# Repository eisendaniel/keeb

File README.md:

# un**ORTHO**dox

Devices

* UNO-XXX are main hosts, direct USB HID devices
* DOX-XXX are I2C expansion modules, connected via TRRS to the I2C bus and 5V power rails

## **UNO-W14** : 14x5 ortholinear keyboard

## **DOX**-XXX : I2C expansion modules

[TODO] ... space for future development

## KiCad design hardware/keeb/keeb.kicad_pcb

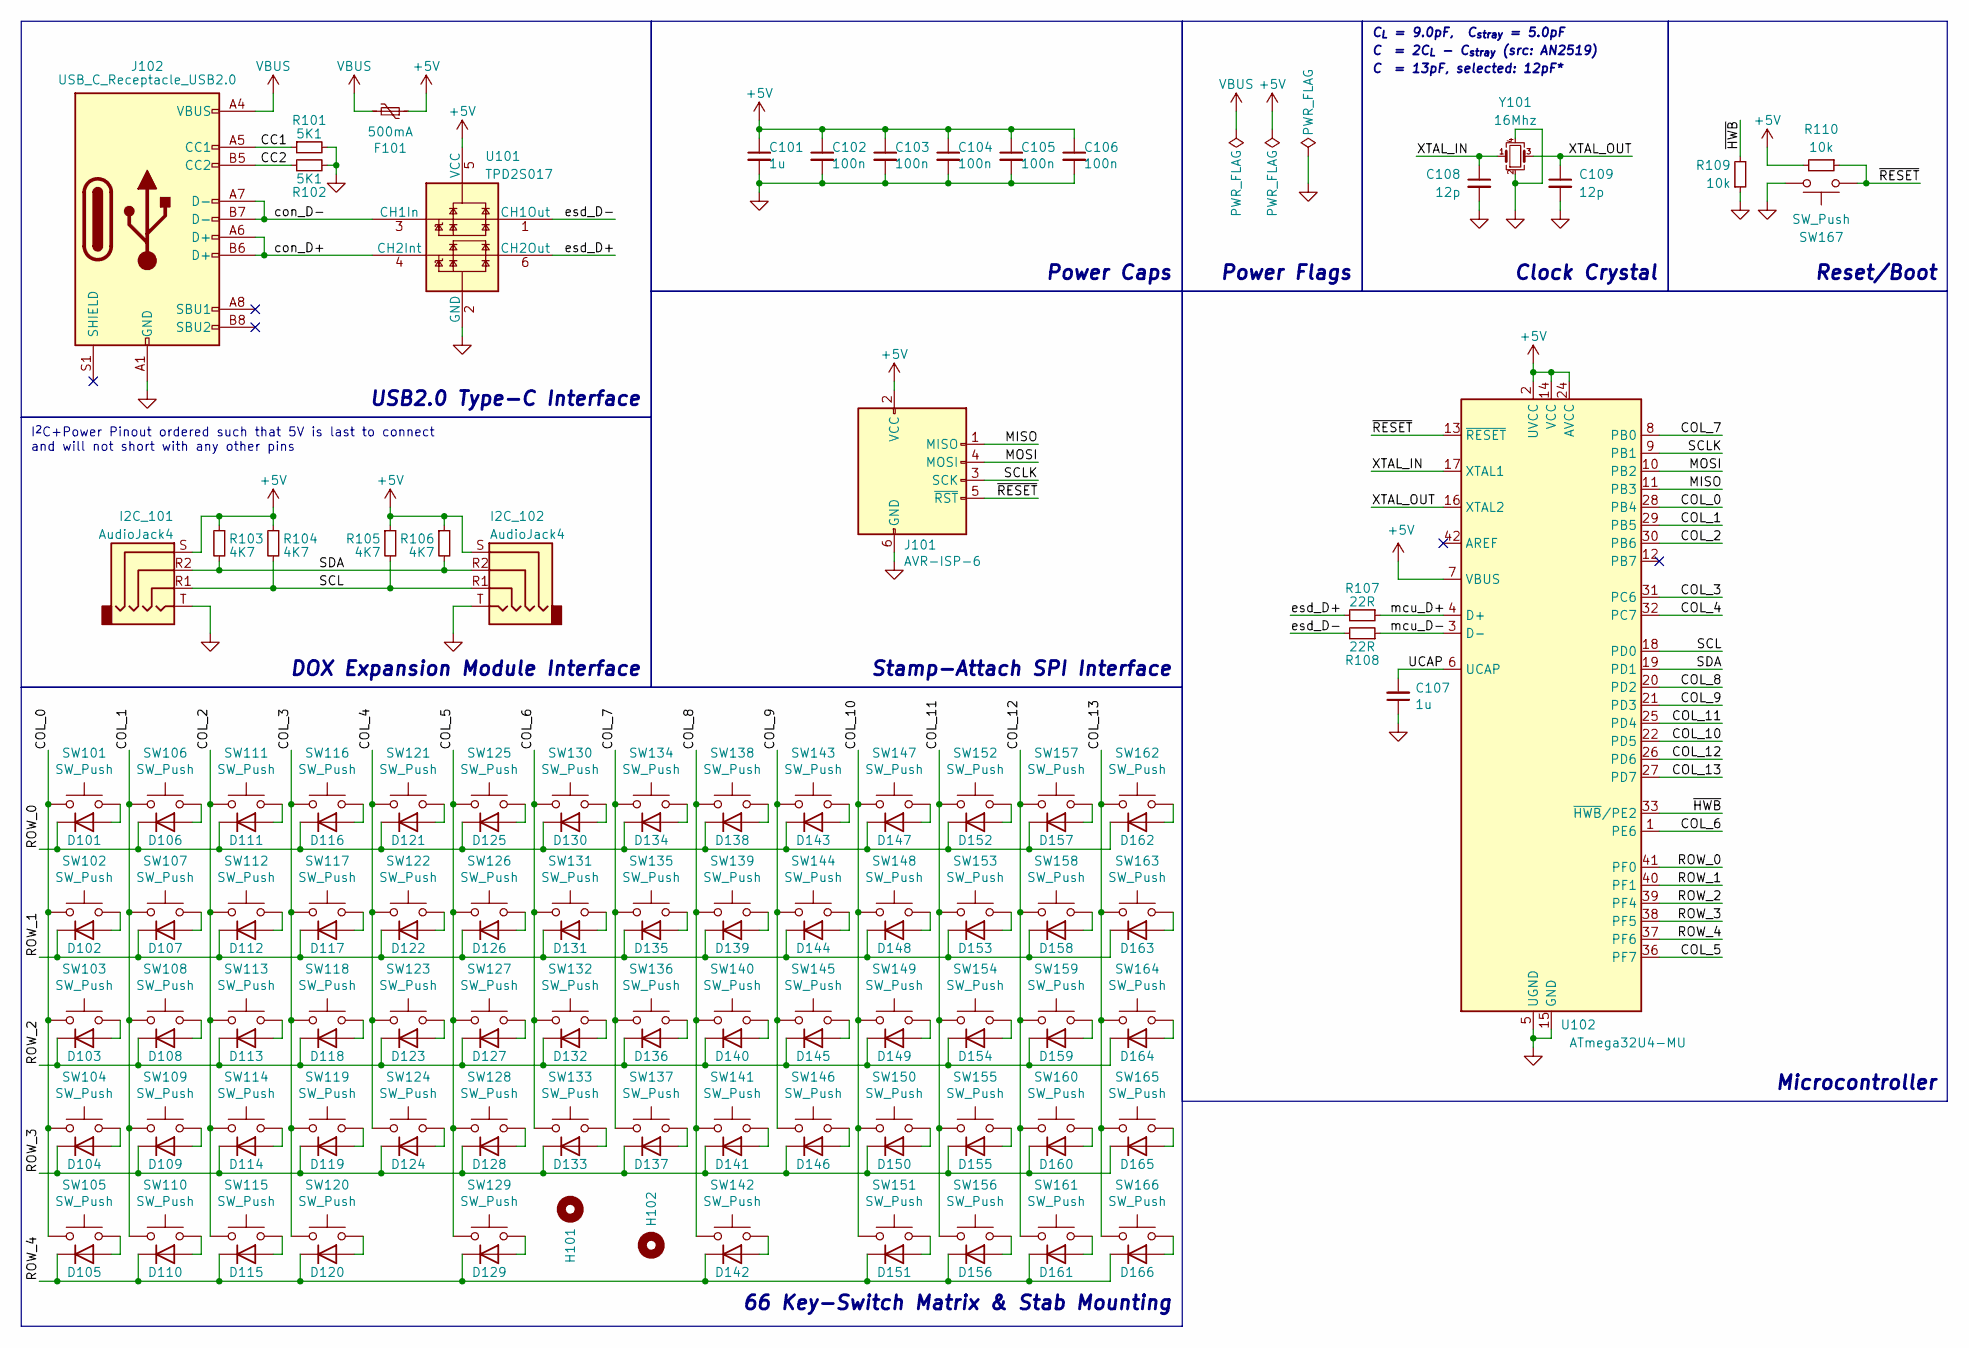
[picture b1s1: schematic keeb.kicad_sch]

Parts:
C101, C107: 1u; C_0603_1608Metric; LCSC # C15849
C102, C103, C104, C105, C106: 100n; C_0402_1005Metric; LCSC # C1525
C108, C109: 12p; C_0402_1005Metric; LCSC # C1547
D101, D102, D103, D104, D105, D106, D107, D108, D109, D110, D111, D112, D113, D114, D115, D116, D117, D118, D119, D120, D121, D122, D123, D124, D125, D126, D127, D128, D129, D130, D131, D132, D133, D134, D135, D136, D137, D138, D139, D140, D141, D142, D143, D144, D145, D146, D147, D148, D149, D150, D151, D152, D153, D154, D155, D156, D157, D158, D159, D160, D161, D162, D163, D164, D165, D166: D; D_SOD-123F; LCSC # C64898
F101: 500mA; Fuse_0603_1608Metric; LCSC # C369159
H101, H102: MountingHole; Stabilizer_Cherry_MX_3.00u
I2C_101, I2C_102: AudioJack4; Jack_3.5mm_TIC54-00177_Horizontal; LCSC # C388632
J101: AVR-ISP-6; Stamp-Attach_SA2030-IDC-NL_2x03_P1.27mm_Vertical
J102: USB_C_Receptacle_USB2.0; USB_C_Receptacle_HRO_TYPE-C-31-M-12; LCSC # C165948
R101, R102: 5K1; R_0402_1005Metric; LCSC # C25905
R103, R104, R105, R106: 4K7; R_0402_1005Metric; LCSC # C25900
R107, R108: 22R; R_0402_1005Metric; LCSC # C25092
R109, R110: 10k; R_0402_1005Metric; LCSC # C25744
SW101, SW102, SW103, SW104, SW105, SW106, SW107, SW108, SW109, SW110, SW111, SW112, SW113, SW114, SW115, SW116, SW117, SW118, SW119, SW120, SW121, SW122, SW123, SW124, SW125, SW126, SW127, SW128, SW129, SW130, SW131, SW132, SW133, SW134, SW135, SW136, SW137, SW138, SW139, SW140, SW141, SW142, SW143, SW144, SW145, SW146, SW147, SW148, SW149, SW150, SW151, SW152, SW153, SW154, SW155, SW156, SW157, SW158, SW159, SW160, SW161, SW162, SW163, SW164, SW165, SW166: SW_Push; SW_Cherry_MX_PCB_1.00u
SW167: SW_Push; SW_SPST_B3U-1000P; LCSC # C231329
U101: TPD2S017; SOT-23-6; LCSC # C880115
U102: ATmega32U4-MU; QFN-44-1EP_7x7mm_P0.5mm_EP5.2x5.2mm; LCSC # C112161
Y101: 16Mhz; Crystal_SMD_2016-4Pin_2.0x1.6mm; LCSC # C431146

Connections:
+5V: C101.1, C102.1, C103.1, C104.1, C105.1, C106.1, F101.1, I2C_101.S, I2C_102.S, J101.2 (VCC), R103.1, R104.1, R105.1, R106.1, R110.2, U101.5 (VCC), U102.2 (UVCC), U102.7 (VBUS), U102.14 (VCC), U102.24 (AVCC), U102.34 (VCC), U102.44 (AVCC)
/CC1: J102.A5 (CC1), R101.1
/CC2: J102.B5 (CC2), R102.1
/COL_0: SW101.1, SW102.1, SW103.1, SW104.1, SW105.1, U102.28 (PB4)
/COL_1: SW106.1, SW107.1, SW108.1, SW109.1, SW110.1, U102.29 (PB5)
/COL_2: SW111.1, SW112.1, SW113.1, SW114.1, SW115.1, U102.30 (PB6)
/COL_3: SW116.1, SW117.1, SW118.1, SW119.1, SW120.1, U102.31 (PC6)
/COL_4: SW121.1, SW122.1, SW123.1, SW124.1, U102.32 (PC7)
/COL_5: SW125.1, SW126.1, SW127.1, SW128.1, SW129.1, U102.36 (PF7)
/COL_6: SW130.1, SW131.1, SW132.1, SW133.1, U102.1 (PE6)
/COL_7: SW134.1, SW135.1, SW136.1, SW137.1, U102.8 (PB0)
/COL_8: SW138.1, SW139.1, SW140.1, SW141.1, SW142.1, U102.20 (PD2)
/COL_9: SW143.1, SW144.1, SW145.1, SW146.1, U102.21 (PD3)
/COL_10: SW147.1, SW148.1, SW149.1, SW150.1, SW151.1, U102.22 (PD5)
/COL_11: SW152.1, SW153.1, SW154.1, SW155.1, SW156.1, U102.25 (PD4)
/COL_12: SW157.1, SW158.1, SW159.1, SW160.1, SW161.1, U102.26 (PD6)
/COL_13: SW162.1, SW163.1, SW164.1, SW165.1, SW166.1, U102.27 (PD7)
/MISO: J101.1 (MISO), U102.11 (PB3)
/MOSI: J101.4 (MOSI), U102.10 (PB2)
/ROW_0: D101.1 (K), D106.1 (K), D111.1 (K), D116.1 (K), D121.1 (K), D125.1 (K), D130.1 (K), D134.1 (K), D138.1 (K), D143.1 (K), D147.1 (K), D152.1 (K), D157.1 (K), D162.1 (K), U102.41 (PF0)
/ROW_1: D102.1 (K), D107.1 (K), D112.1 (K), D117.1 (K), D122.1 (K), D126.1 (K), D131.1 (K), D135.1 (K), D139.1 (K), D144.1 (K), D148.1 (K), D153.1 (K), D158.1 (K), D163.1 (K), U102.40 (PF1)
/ROW_2: D103.1 (K), D108.1 (K), D113.1 (K), D118.1 (K), D123.1 (K), D127.1 (K), D132.1 (K), D136.1 (K), D140.1 (K), D145.1 (K), D149.1 (K), D154.1 (K), D159.1 (K), D164.1 (K), U102.39 (PF4)
/ROW_3: D104.1 (K), D109.1 (K), D114.1 (K), D119.1 (K), D124.1 (K), D128.1 (K), D133.1 (K), D137.1 (K), D141.1 (K), D146.1 (K), D150.1 (K), D155.1 (K), D160.1 (K), D165.1 (K), U102.38 (PF5)
/ROW_4: D105.1 (K), D110.1 (K), D115.1 (K), D120.1 (K), D129.1 (K), D142.1 (K), D151.1 (K), D156.1 (K), D161.1 (K), D166.1 (K), U102.37 (PF6)
/SCL: I2C_101.R1, I2C_102.R1, R104.2, R105.2, U102.18 (PD0)
/SCLK: J101.3 (SCK), U102.9 (PB1)
/SDA: I2C_101.R2, I2C_102.R2, R103.2, R106.2, U102.19 (PD1)
/UCAP: C107.2, U102.6 (UCAP)
/XTAL_IN: C108.1, U102.17 (XTAL1), Y101.1
/XTAL_OUT: C109.1, U102.16 (XTAL2), Y101.3
/con_D+: J102.A6 (D+), J102.B6 (D+), U101.4 (CH2Int)
/con_D-: J102.A7 (D-), J102.B7 (D-), U101.3 (CH1In)
/esd_D+: R107.2, U101.6 (CH2Out)
/esd_D-: R108.2, U101.1 (CH1Out)
/mcu_D+: R107.1, U102.4 (D+)
/mcu_D-: R108.1, U102.3 (D-)
/~HWB: R109.2, U102.33 (~HWB/PE2)
/~RESET: J101.5 (~RST), R110.1, SW167.1, U102.13 (~RESET)
GND: C101.2, C102.2, C103.2, C104.2, C105.2, C106.2, C107.1, C108.2, C109.2, I2C_101.T, I2C_102.T, J101.6 (GND), J102.A1 (GND), J102.A12 (GND), J102.B1 (GND), J102.B12 (GND), R101.2, R102.2, R109.1, SW167.2, U101.2 (GND), U102.5 (UGND), U102.15 (GND), U102.23 (GND), U102.35 (GND), U102.43 (GND), U102.45 (GND), Y101.2, Y101.4
unnamed: D101.2 (A), SW101.2
unnamed: D102.2 (A), SW102.2
unnamed: D103.2 (A), SW103.2
unnamed: D104.2 (A), SW104.2
unnamed: D105.2 (A), SW105.2
unnamed: D106.2 (A), SW106.2
unnamed: D107.2 (A), SW107.2
unnamed: D108.2 (A), SW108.2
unnamed: D109.2 (A), SW109.2
unnamed: D110.2 (A), SW110.2
unnamed: D111.2 (A), SW111.2
unnamed: D112.2 (A), SW112.2
unnamed: D113.2 (A), SW113.2
unnamed: D114.2 (A), SW114.2
unnamed: D115.2 (A), SW115.2
unnamed: D116.2 (A), SW116.2
unnamed: D117.2 (A), SW117.2
unnamed: D118.2 (A), SW118.2
unnamed: D119.2 (A), SW119.2
unnamed: D120.2 (A), SW120.2
unnamed: D121.2 (A), SW121.2
unnamed: D122.2 (A), SW122.2
unnamed: D123.2 (A), SW123.2
unnamed: D124.2 (A), SW124.2
unnamed: D125.2 (A), SW125.2
unnamed: D126.2 (A), SW126.2
unnamed: D127.2 (A), SW127.2
unnamed: D128.2 (A), SW128.2
unnamed: D129.2 (A), SW129.2
unnamed: D130.2 (A), SW130.2
unnamed: D131.2 (A), SW131.2
unnamed: D132.2 (A), SW132.2
unnamed: D133.2 (A), SW133.2
unnamed: D134.2 (A), SW134.2
unnamed: D135.2 (A), SW135.2
unnamed: D136.2 (A), SW136.2
unnamed: D137.2 (A), SW137.2
unnamed: D138.2 (A), SW138.2
unnamed: D139.2 (A), SW139.2
unnamed: D140.2 (A), SW140.2
unnamed: D141.2 (A), SW141.2
unnamed: D142.2 (A), SW142.2
unnamed: D143.2 (A), SW143.2
unnamed: D144.2 (A), SW144.2
unnamed: D145.2 (A), SW145.2
unnamed: D146.2 (A), SW146.2
unnamed: D147.2 (A), SW147.2
unnamed: D148.2 (A), SW148.2
unnamed: D149.2 (A), SW149.2
unnamed: D150.2 (A), SW150.2
unnamed: D151.2 (A), SW151.2
unnamed: D152.2 (A), SW152.2
unnamed: D153.2 (A), SW153.2
unnamed: D154.2 (A), SW154.2
unnamed: D155.2 (A), SW155.2
unnamed: D156.2 (A), SW156.2
unnamed: D157.2 (A), SW157.2
unnamed: D158.2 (A), SW158.2
unnamed: D159.2 (A), SW159.2
unnamed: D160.2 (A), SW160.2
unnamed: D161.2 (A), SW161.2
unnamed: D162.2 (A), SW162.2
unnamed: D163.2 (A), SW163.2
unnamed: D164.2 (A), SW164.2
unnamed: D165.2 (A), SW165.2
unnamed: D166.2 (A), SW166.2
VBUS: F101.2, J102.A4 (VBUS), J102.A9 (VBUS), J102.B4 (VBUS), J102.B9 (VBUS)

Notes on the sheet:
Reset/Boot
DOX Expansion Module Interface
Power Caps
Power Flags
Clock Crystal
C_{L} = 9.0pF, C_{stray} = 5.0pF
C_{ } = 2C_{L} - C_{stray} (src: AN2519)
I^{2}C+Power Pinout ordered such that 5V is last to connect and will not short with any other pins
C_{ } = 13pF, selected: 12pF*
USB2.0 Type-C Interface
Microcontroller
66 Key-Switch Matrix & Stab Mounting
Stamp-Attach SPI Interface

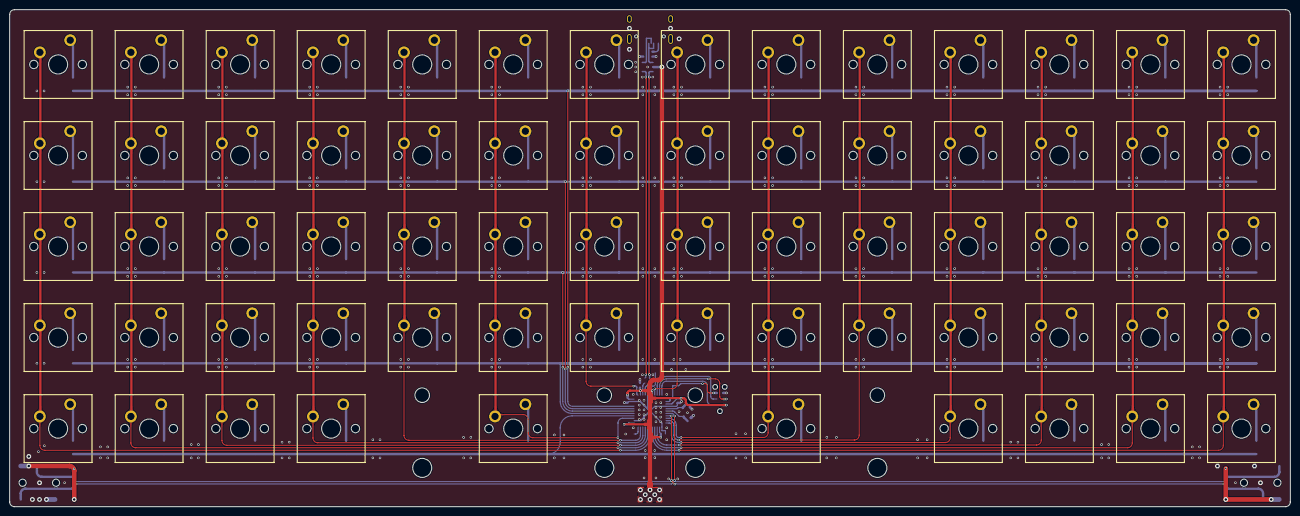
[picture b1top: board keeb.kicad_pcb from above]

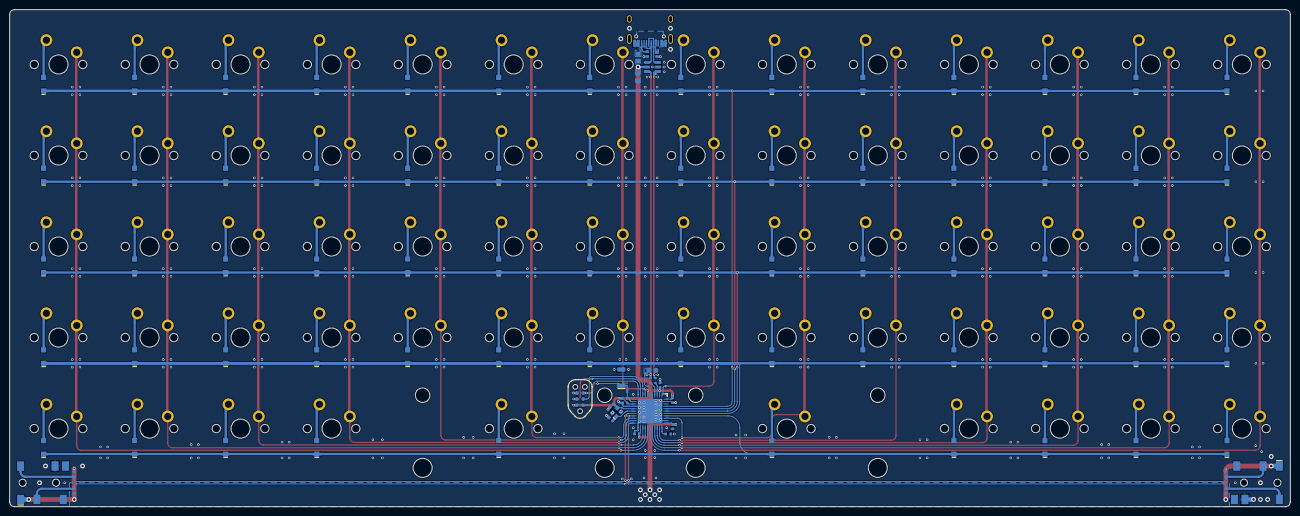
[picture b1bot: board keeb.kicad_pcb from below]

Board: 2 copper layers, 268.0 x 104.0 mm, 162 parts (94 on the bottom side), 106 nets.

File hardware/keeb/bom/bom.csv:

"Reference","Value","Footprint","Datasheet","LCSC #","LCSC Link","Qty"
"C101, C107","1u","unORTHOdox:C_0603_1608Metric","https://datasheet.lcsc.com/lcsc/1810261812_Samsung-Electro-M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","C15849","https://lcsc.com/product-detail/Multilayer-Ceramic-Capacitor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","2"
"C102-C106","100n","unORTHOdox:C_0402_1005Metric","https://datasheet.lcsc.com/lcsc/1810191219_Samsung-Electro-M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","C1525","https://www.lcsc.com/product-detail/Multilayer-Ceramic-Capac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","5"
"C108, C109","12p","unORTHOdox:C_0402_1005Metric","https://datasheet.lcsc.com/lcsc/1811141710_FH--Guangdong-Fen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","C1547","https://www.lcsc.com/product-detail/Multilayer-Ceramic-Capac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","2"
"D101-D166","D","unORTHOdox:D_SOD-123F","https://datasheet.lcsc.com/lcsc/1809301215_MDD-Microdiode-El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","C64898","https://www.lcsc.com/product-detail/Diodes---General-Purpose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","66"
"F101","500mA","unORTHOdox:Fuse_0603_1608Metric","https://datasheet.lcsc.com/lcsc/1912111437_Jinrui-Electronic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","C369159","https://www.lcsc.com/product-detail/Resettable-Fuses_Jinrui-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","1"
"H101, H102","MountingHole","PCM_Mounting_Keyboard_Stabilizer:Stabilizer_Cherry_MX_3.00u","~","","","2"
"I2C_101, I2C_102","AudioJack4","unORTHOdox:Jack_3.5mm_TIC54-00177_Horizontal","https://datasheet.lcsc.com/lcsc/2110151730_XKB-Connectivity-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","C388632","https://www.lcsc.com/product-detail/Audio-Connectors_XKB-Con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","2"
"J101","AVR-ISP-6","Stamp_Attach:Stamp-Attach_SA2030-IDC-NL_2x03_P1.27mm_Vertical"," ~","","","1"
"J102","USB_C_Receptacle_USB2.0","unORTHOdox:USB_C_Receptacle_HRO_TYPE-C-31-M-12","https://datasheet.lcsc.com/lcsc/2205251630_Korean-Hroparts-E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","C165948","https://www.lcsc.com/product-detail/USB-Connectors_Korean-Hr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","1"
"R101, R102","5K1","unORTHOdox:R_0402_1005Metric","https://datasheet.lcsc.com/lcsc/2206010045_UNI-ROYAL-Uniroya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","C25905","https://www.lcsc.com/product-detail/Chip-Resistor---Surface-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","2"
"R103-R106","4K7","unORTHOdox:R_0402_1005Metric","https://datasheet.lcsc.com/lcsc/2206010045_UNI-ROYAL-Uniroya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","C25900","https://www.lcsc.com/product-detail/Chip-Resistor---Surface-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","4"
"R107, R108","22R","unORTHOdox:R_0402_1005Metric","https://datasheet.lcsc.com/lcsc/2205311900_UNI-ROYAL-Uniroya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","C25092","https://lcsc.com/product-detail/Chip-Resistor---Surface-Moun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","2"
"R109, R110","10k","unORTHOdox:R_0402_1005Metric","https://datasheet.lcsc.com/lcsc/2206010100_UNI-ROYAL-Uniroya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","C25744","https://www.lcsc.com/product-detail/Chip-Resistor---Surface-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","2"
"SW101-SW166","SW_Push","PCM_Switch_Keyboard_Cherry_MX:SW_Cherry_MX_PCB_1.00u","~","","","66"
"SW167","SW_Push","unORTHOdox:SW_SPST_B3U-1000P","https://datasheet.lcsc.com/lcsc/1810010153_Omron-Electronics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","C231329","https://www.lcsc.com/product-detail/Tactile-Switches_Omron-E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","1"
"U101","TPD2S017","unORTHOdox:SOT-23-6","http://www.ti.com/lit/ds/symlink/tpd2s017.pdf","C880115","https://www.lcsc.com/product-detail/ESD-Protection-Devices_T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","1"
"U102","ATmega32U4-MU","unORTHOdox:QFN-44-1EP_7x7mm_P0.5mm_EP5.2x5.2mm","http://ww1.microchip.com/downloads/en/DeviceDoc/Atmel-7766-8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","C112161","https://www.lcsc.com/product-detail/Microcontroller-Units-MC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","1"
"Y101","16Mhz","unORTHOdox:Crystal_SMD_2016-4Pin_2.0x1.6mm","https://datasheet.lcsc.com/lcsc/1912111437_YL-Failong-Crysta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","C431146","https://www.lcsc.com/product-detail/Crystals_YLFailong-Cryst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","1"

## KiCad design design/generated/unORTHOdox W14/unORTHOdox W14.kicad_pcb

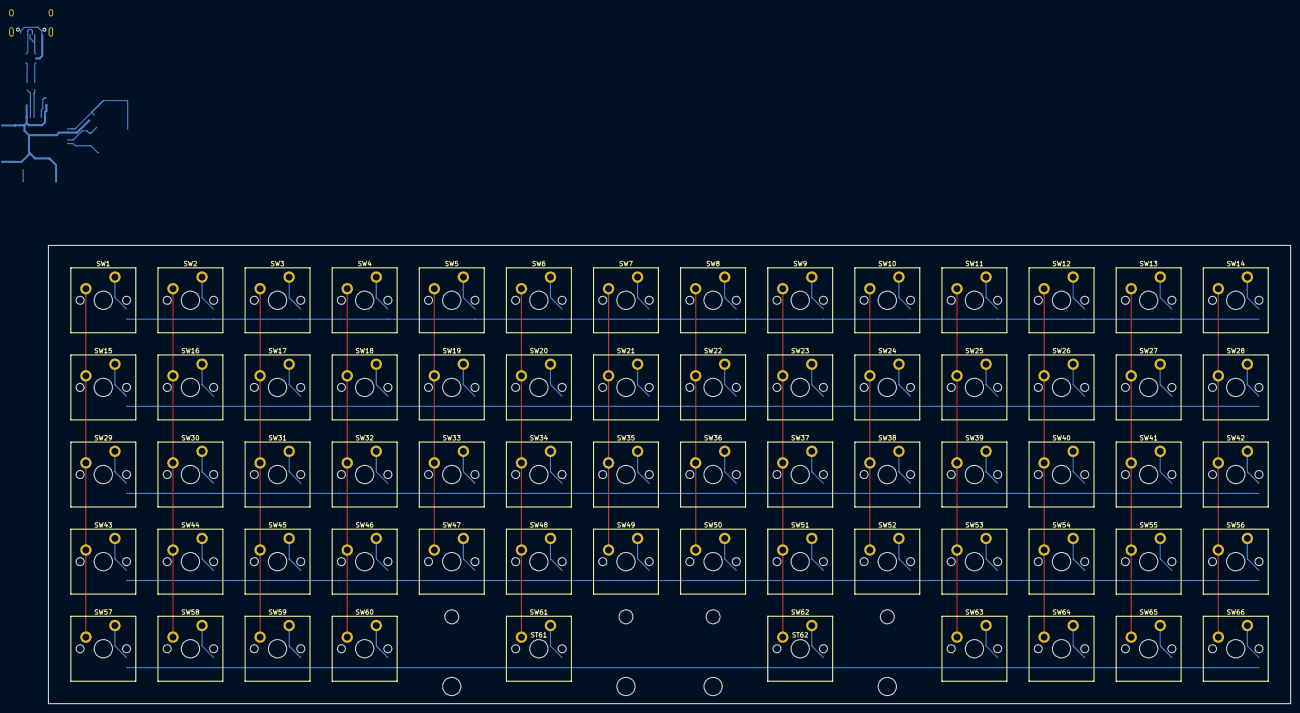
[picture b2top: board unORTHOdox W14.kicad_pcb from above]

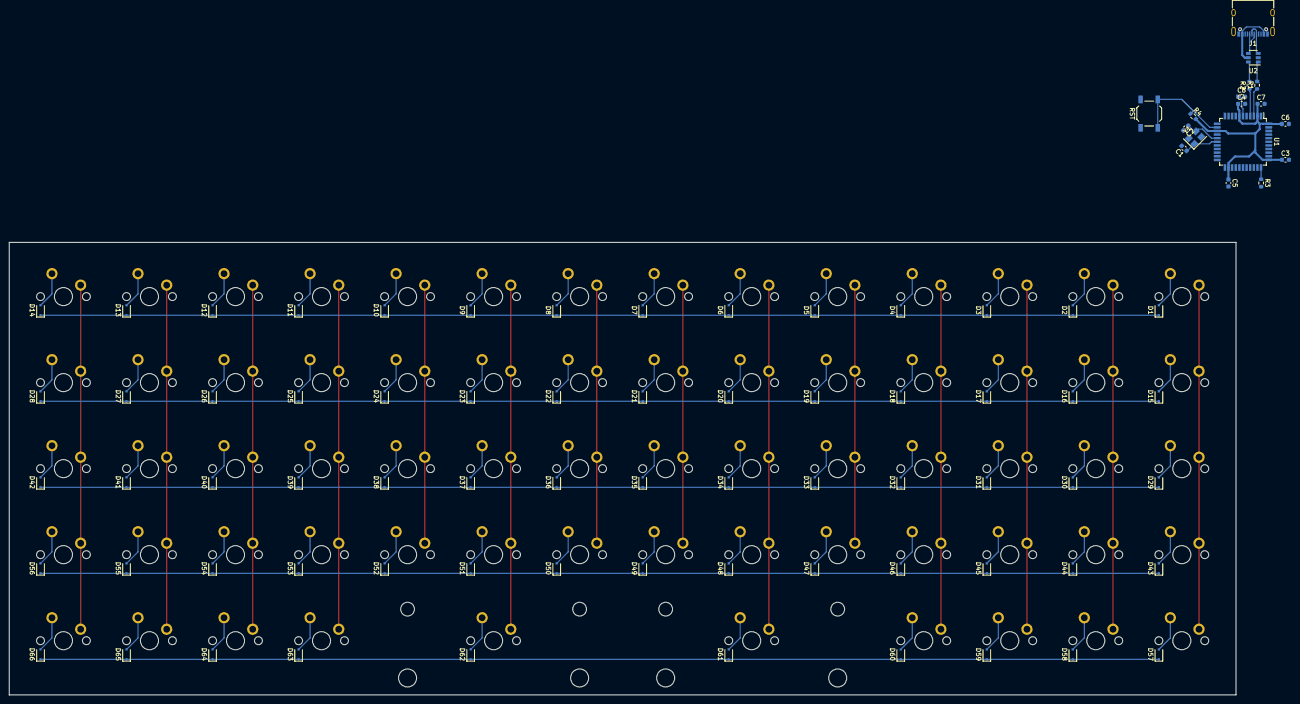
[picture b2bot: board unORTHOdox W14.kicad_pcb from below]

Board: 2 copper layers, 271.7 x 100.2 mm, 151 parts (83 on the bottom side), 98 nets.

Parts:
C1, C2: 22p; C_0603_1608Metric
C3, C4, C5, C6: 0.1u; C_0603_1608Metric
C7: 4.7u; C_0603_1608Metric
C8: 1u; C_0603_1608Metric
D1, D2, D3, D4, D5, D6, D7, D8, D9, D10, D11, D12, D13, D14, D15, D16, D17, D18, D19, D20, D21, D22, D23, D24, D25, D26, D27, D28, D29, D30, D31, D32, D33, D34, D35, D36, D37, D38, D39, D40, D41, D42, D43, D44, D45, D46, D47, D48, D49, D50, D51, D52, D53, D54, D55, D56, D57, D58, D59, D60, D61, D62, D63, D64, D65, D66: D; D_SOD-323F
J1: USB_C_Receptacle_USB2.0; USB_C_Receptacle_XKB_U262-16XN-4BVC11
R1, R2: 22; R_0603_1608Metric
R3, R4: 10k; R_0603_1608Metric
RST: SW_SPST; SW_SPST_TL3342
ST61, ST62: MountingHole; Stabilizer_Cherry_MX_3u
SW1, SW2, SW3, SW4, SW5, SW6, SW7, SW8, SW9, SW10, SW11, SW12, SW13, SW14, SW15, SW16, SW17, SW18, SW19, SW20, SW21, SW22, SW23, SW24, SW25, SW26, SW27, SW28, SW29, SW30, SW31, SW32, SW33, SW34, SW35, SW36, SW37, SW38, SW39, SW40, SW41, SW42, SW43, SW44, SW45, SW46, SW47, SW48, SW49, SW50, SW51, SW52, SW53, SW54, SW55, SW56, SW57, SW58, SW59, SW60, SW63, SW64, SW65, SW66: SW_Push; SW_Cherry_MX_PCB_1.00u
SW61, SW62: SW_Push; SW_Cherry_MX_PCB_3.00u
U1: ATmega16U4-AU; TQFP-44_10x10mm_P0.8mm
U2: TPD2S017; SOT-23-6
Y1: Crystal_GND24; Crystal_SMD_3225-4Pin_3.2x2.5mm

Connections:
COL0: SW1.1, SW15.1, SW29.1, SW43.1, SW57.1, U1.29
COL1: SW2.1, SW16.1, SW30.1, SW44.1, SW58.1, U1.30
COL2: SW3.1, SW17.1, SW31.1, SW45.1, SW59.1, U1.12
COL3: SW4.1, SW18.1, SW32.1, SW46.1, SW60.1, U1.31
COL4: SW5.1, SW19.1, SW33.1, SW47.1, U1.32
COL5: SW6.1, SW20.1, SW34.1, SW48.1, SW61.1, U1.18
COL6: SW7.1, SW21.1, SW35.1, SW49.1, U1.19
COL7: SW8.1, SW22.1, SW36.1, SW50.1, U1.20
COL8: SW9.1, SW23.1, SW37.1, SW51.1, SW62.1, U1.21
COL9: SW10.1, SW24.1, SW38.1, SW52.1, U1.25
COL10: SW11.1, SW25.1, SW39.1, SW53.1, SW63.1, U1.22
COL11: SW12.1, SW26.1, SW40.1, SW54.1, SW64.1, U1.26
COL12: SW13.1, SW27.1, SW41.1, SW55.1, SW65.1, U1.27
COL13: SW14.1, SW28.1, SW42.1, SW56.1, SW66.1, U1.41
GND: C1.2, C2.2, C3.2, C4.2, C5.2, C6.2, C7.2, C8.2, J1.A1, J1.A12, J1.B1, J1.B12, J1.S1, R3.2, RST.1, U1.5, U1.15, U1.23, U1.35, U1.43, U2.2, Y1.2, Y1.4
unnamed: D1.2, SW1.2
unnamed: D2.2, SW2.2
unnamed: D3.2, SW3.2
unnamed: D4.2, SW4.2
unnamed: D5.2, SW5.2
unnamed: D6.2, SW6.2
unnamed: D7.2, SW7.2
unnamed: D8.2, SW8.2
unnamed: D9.2, SW9.2
unnamed: D10.2, SW10.2
unnamed: D11.2, SW11.2
unnamed: D12.2, SW12.2
unnamed: D13.2, SW13.2
unnamed: D14.2, SW14.2
unnamed: D15.2, SW15.2
unnamed: D16.2, SW16.2
unnamed: D17.2, SW17.2
unnamed: D18.2, SW18.2
unnamed: D19.2, SW19.2
unnamed: D20.2, SW20.2
unnamed: D21.2, SW21.2
unnamed: D22.2, SW22.2
unnamed: D23.2, SW23.2
unnamed: D24.2, SW24.2
unnamed: D25.2, SW25.2
unnamed: D26.2, SW26.2
unnamed: D27.2, SW27.2
unnamed: D28.2, SW28.2
unnamed: D29.2, SW29.2
unnamed: D30.2, SW30.2
unnamed: D31.2, SW31.2
unnamed: D32.2, SW32.2
unnamed: D33.2, SW33.2
unnamed: D34.2, SW34.2
unnamed: D35.2, SW35.2
unnamed: D36.2, SW36.2
unnamed: D37.2, SW37.2
unnamed: D38.2, SW38.2
unnamed: D39.2, SW39.2
unnamed: D40.2, SW40.2
unnamed: D41.2, SW41.2
unnamed: D42.2, SW42.2
unnamed: D43.2, SW43.2
unnamed: D44.2, SW44.2
unnamed: D45.2, SW45.2
unnamed: D46.2, SW46.2
unnamed: D47.2, SW47.2
unnamed: D48.2, SW48.2
unnamed: D49.2, SW49.2
unnamed: D50.2, SW50.2
unnamed: D51.2, SW51.2
unnamed: D52.2, SW52.2
unnamed: D53.2, SW53.2
unnamed: D54.2, SW54.2
unnamed: D55.2, SW55.2
unnamed: D56.2, SW56.2
unnamed: D57.2, SW57.2
unnamed: D58.2, SW58.2
unnamed: D59.2, SW59.2
unnamed: D60.2, SW60.2
unnamed: D61.2, SW61.2
unnamed: D62.2, SW62.2
unnamed: D63.2, SW63.2
unnamed: D64.2, SW64.2
unnamed: D65.2, SW65.2
unnamed: D66.2, SW66.2
ROW0: D1.1, D2.1, D3.1, D4.1, D5.1, D6.1, D7.1, D8.1, D9.1, D10.1, D11.1, D12.1, D13.1, D14.1, U1.8
ROW1: D15.1, D16.1, D17.1, D18.1, D19.1, D20.1, D21.1, D22.1, D23.1, D24.1, D25.1, D26.1, D27.1, D28.1, U1.9
ROW2: D29.1, D30.1, D31.1, D32.1, D33.1, D34.1, D35.1, D36.1, D37.1, D38.1, D39.1, D40.1, D41.1, D42.1, U1.10
ROW3: D43.1, D44.1, D45.1, D46.1, D47.1, D48.1, D49.1, D50.1, D51.1, D52.1, D53.1, D54.1, D55.1, D56.1, U1.11
ROW4: D57.1, D58.1, D59.1, D60.1, D61.1, D62.1, D63.1, D64.1, D65.1, D66.1, U1.28
VCC: C3.1, C4.1, C5.1, C6.1, C7.1, J1.A4, J1.A9, J1.B4, J1.B9, R4.2, U1.2, U1.14, U1.24, U1.34, U1.44, U2.5
mcu/D+: R2.1, U1.4
mcu/D-: R1.1, U1.3
mcu/UCAP: C8.1, U1.6
mcu/XTAL1: C1.1, U1.17, Y1.1
mcu/XTAL2: C2.1, U1.16, Y1.3
mcu/~HWB~/PE2: R3.1, U1.33
mcu/~RESET: R4.1, RST.2, U1.13
u2/D+: R2.2, U2.6
u2/D-: R1.2, U2.1
usb/D+: J1.A6, J1.B6, U2.4
usb/D-: J1.A7, J1.B7, U2.3

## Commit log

2021-11-23 init
2021-11-23 keeb
2021-11-24 schem compl, layout sw, mat routing
2021-11-25 col, USB, and gnd layout
2021-11-25 models3D
2021-11-25 first pass layout complete
2021-11-25 lp rst sw
2021-11-25 added plate subdir
2021-11-25 plate brd size
2021-11-26 reset route cleanup
2021-11-26 usb width delta trans
2021-11-26 plate edge cuts
2021-11-26 plate fill
2021-11-26 dims
2021-11-26 kdims
2021-11-26 USB power cleanup
2021-11-26 del cad
2021-11-26 unpop ISP
2021-11-26 uniform diode routes
2021-11-26 cache
2021-11-27 CLOSED PLATE
2021-11-28 i2c fin
2021-11-28 updated bulk decoupling and usb-c routing
2021-11-28 USB power pour alignment
2021-11-28 update I2C routing
2021-11-28 DSA keycap mods
2021-11-29 fixed f mask fp
2021-11-29 silk cleanu
2021-11-29 copper pour filling, mounting m2 holes pass 1
2021-11-29 img rdme
2021-12-02 sync
2021-12-09 recolor step
2021-12-15 fix sw mod and left over routing cleaning
2021-12-16 logo begin
2022-01-11 kicad 6 upgrade
2022-01-16 clean trace
2022-01-18 qfn layout complete
2022-01-19 curvin
2022-01-26 trace widths unified
2022-01-26 5V clean
2022-01-26 complete via stitch
2022-01-26 5V curved
2022-01-26 origin and step
2022-01-26 plate resize
2023-03-07 RESTART: Version2
2023-03-07 footprints/general libs redone
2023-03-07 crtyrd and versioning of fp
2023-03-08 matrix and row/colrouting
2023-03-09 usb/matrix/mcu routing
2023-03-09 layout cont, fp mcu updated
2023-03-10 footprints, part selection, cleanupo
2023-03-10 row and col via and trace spacing and fillets
2023-03-10 First Routing Pass Complete
2023-03-11 LCSC part selected
2023-03-11 route cleanup
2023-03-13 all FP cleaned up and updated
2023-03-13 image exports and crystal model
2023-03-13 render
2023-03-14 HTML Bom, osc load cap redo and schem org
2023-03-14 repo reorg and PCB complete (pre fabhouse specifics)
2023-03-14 ignore
2023-03-14 final parts and LCSC bom
2023-03-15 fp pin1 cleanup and general route polish (focus on i2c)
2023-03-15 plate start
2023-03-16 updated layout and extended i2c jacks
2023-03-17 svg exports for silkscreening
2023-03-21 schem info text, and README updated
